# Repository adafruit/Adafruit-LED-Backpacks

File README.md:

# Adafruit LED Matrix backpacks PCBs

&nbsp; 
&nbsp; 
&nbsp; 
<br />
&nbsp; 
&nbsp; 
&nbsp; 
<br />

What's better than a single LED? Lots of LEDs! A fun way to make a small display is to use an 8x8 matrix or a 4-digit 7-segment display. Matrices like these are 'multiplexed' - so to control all the seven-segment LEDs you need 14 pins. That's a lot of pins, and there are driver chips like the MAX7219 that can control a matrix for you but there's a lot of wiring to set up and they take up a ton of space. Here at Adafruit we feel your pain! After all, wouldn't it be awesome if you could control a matrix without tons of wiring? That's where these adorable LED matrix backpacks come in. We have them in two flavors - a mini 8x8 and a 4-digit 0.56" 7-segment. 

These are the Eagle CAD files for the Adafruit LED Backpack breakouts:
- http://www.adafruit.com/products/878
- http://www.adafruit.com/products/879
- http://www.adafruit.com/products/880
- http://www.adafruit.com/products/881
- http://www.adafruit.com/products/872
- http://www.adafruit.com/products/871
- http://www.adafruit.com/products/870
- https://www.adafruit.com/product/902

These displays use I2C to communicate, 2 pins are required to 
interface. There are multiple selectable I2C addresses. For backpacks 
with 2 Address Select pins: 0x70, 0x71, 0x72 or 0x73. For backpacks 
with 3 Address Select pins: 0x70 thru 0x77

### License

Adafruit invests time and resources providing this open source design, please support Adafruit and open-source hardware by purchasing products from [Adafruit](https://www.adafruit.com)!

All text above must be included in any redistribution

Designed by Limor Fried/Ladyada for Adafruit Industries.
Creative Commons Attribution/Share-Alike, all text above must be included in any redistribution. 
See license.txt for additional information.

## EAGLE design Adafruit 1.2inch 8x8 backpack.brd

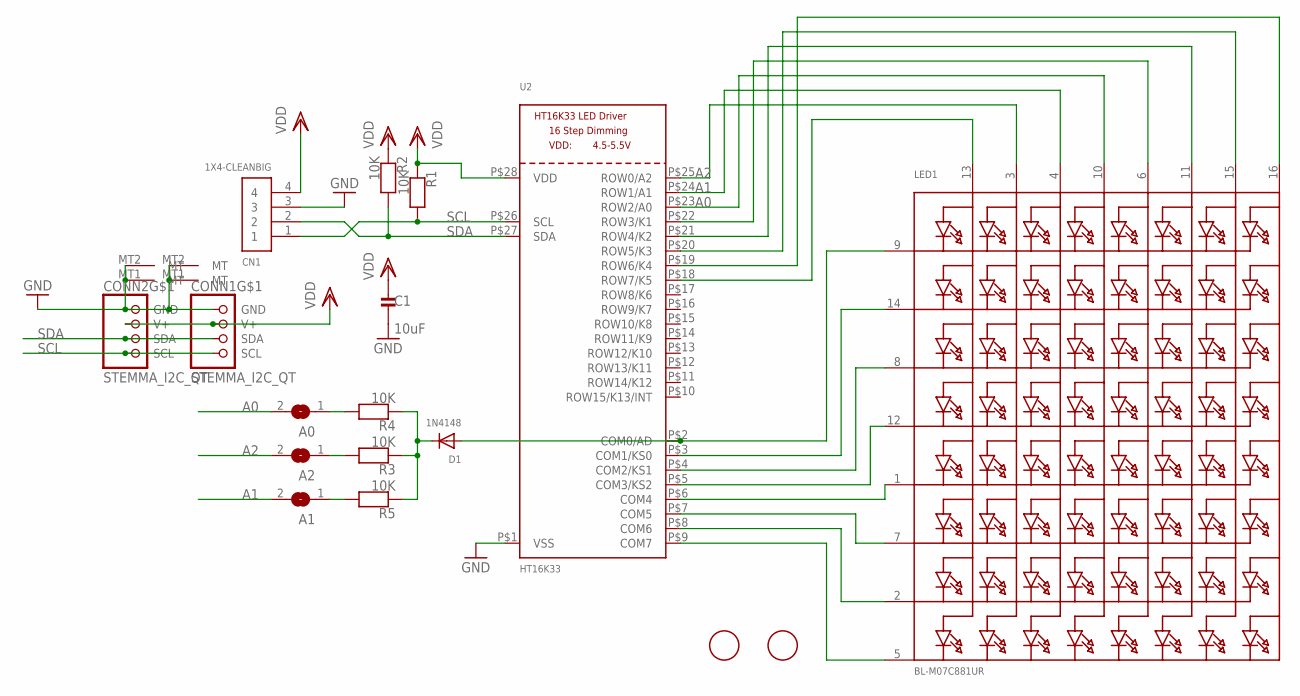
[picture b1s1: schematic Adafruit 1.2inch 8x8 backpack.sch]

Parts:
A0, A1, A2: SOLDERJUMPERREFLOW_NOPASTE; SOLDERJUMPER_REFLOW_NOPASTE
C1: 10uF; 0805-NO
CN1: 1X4-CLEANBIG; 1X04-CLEANBIG
CONN1, CONN2: STEMMA_I2C_QT; JST_SH4
D1: 1N4148; SOD-323
LED1: BL-M07C881UR; SEGMENT_BL-M12A881UR
R1, R2, R3, R4, R5: 10K; 0603-NO
U2: HT16K33; SOP28_300MIL
U$1, U$2: FIDUCIAL; FIDUCIAL_1MM

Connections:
A0: A0.2, LED1.10 (A4), U2.P$23 (ROW2/A0)
A1: A1.2, LED1.4 (A3), U2.P$24 (ROW1/A1)
A2: A2.2, LED1.3 (A2), U2.P$25 (ROW0/A2)
GND: C1.2, CN1.3, CONN1.1 (GND), CONN1.MT1 (MT), CONN1.MT2 (MT), CONN2.1 (GND), CONN2.MT1 (MT), CONN2.MT2 (MT), U2.P$1 (VSS)
unnamed: LED1.5 (K8), U2.P$9 (COM7)
unnamed: LED1.2 (K7), U2.P$8 (COM6)
unnamed: LED1.7 (K6), U2.P$7 (COM5)
unnamed: LED1.1 (K5), U2.P$6 (COM4)
unnamed: LED1.12 (K4), U2.P$5 (COM3/KS2)
unnamed: LED1.8 (K3), U2.P$4 (COM2/KS1)
unnamed: LED1.14 (K2), U2.P$3 (COM1/KS0)
unnamed: D1.A, LED1.9 (K1), U2.P$2 (COM0/AD)
unnamed: A1.1, R5.2
unnamed: LED1.6 (A5), U2.P$22 (ROW3/K1)
unnamed: LED1.11 (A6), U2.P$21 (ROW4/K2)
unnamed: D1.C, R3.1, R4.1, R5.1
unnamed: LED1.13 (A1), U2.P$18 (ROW7/K5)
unnamed: A2.1, R3.2
unnamed: A0.1, R4.2
SCL: CN1.1, CONN1.4 (SCL), CONN2.4 (SCL), R1.2, U2.P$26 (SCL)
SDA: CN1.2, CONN1.3 (SDA), CONN2.3 (SDA), R2.2, U2.P$27 (SDA)
SEG_F: LED1.15 (A7), U2.P$20 (ROW5/K3)
SEG_G: LED1.16 (A8), U2.P$19 (ROW6/K4)
VDD: C1.1, CN1.4, CONN1.2 (V+), CONN2.2 (V+), R1.1, R2.1, U2.P$28 (VDD)

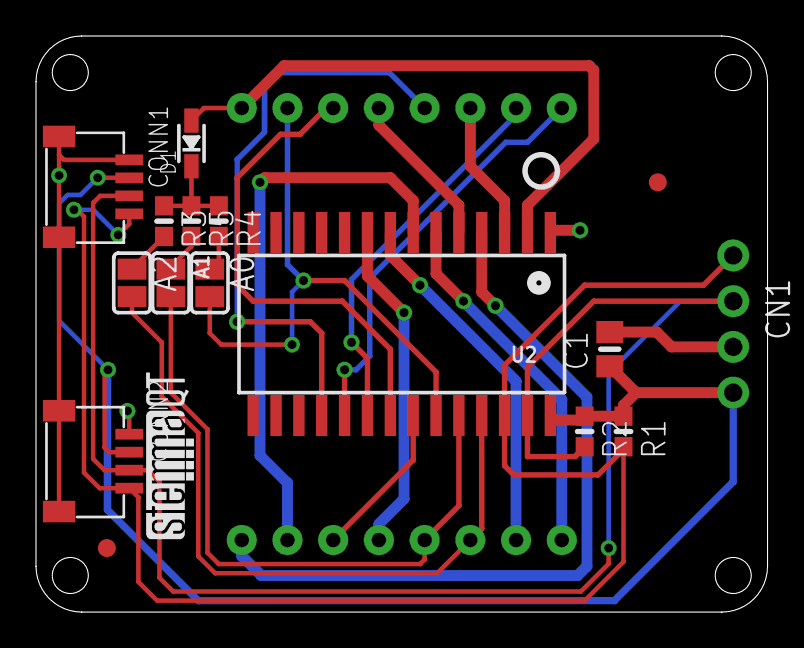
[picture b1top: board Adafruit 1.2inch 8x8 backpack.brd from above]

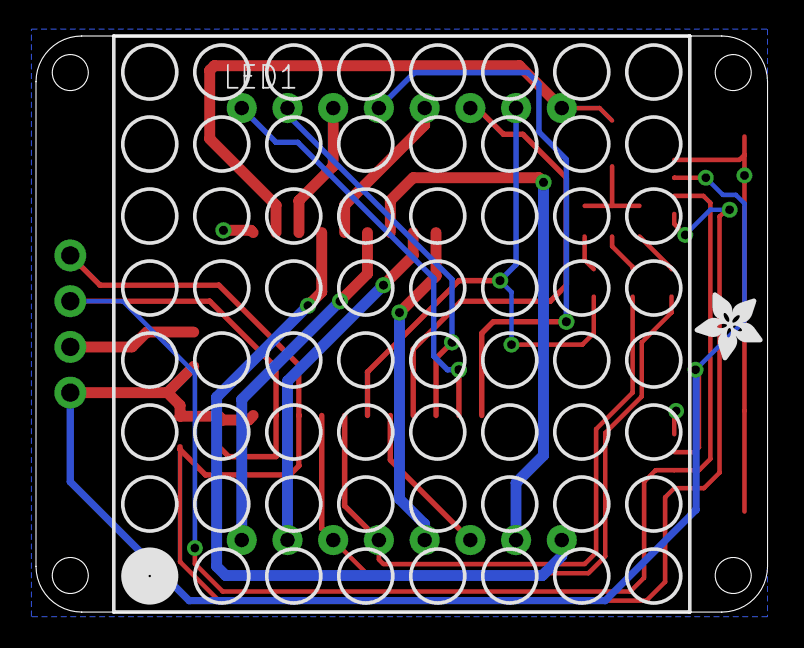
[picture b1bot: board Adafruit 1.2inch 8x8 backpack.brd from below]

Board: 2 copper layers, 40.6 x 32.0 mm, 34 parts (6 on the bottom side), 24 nets.

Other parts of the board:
PLABEL0: PLABEL0
PLABEL1: PLABEL1
PLABEL2: PLABEL2
PLABEL3: PLABEL3
PLABEL4: PLABEL4
PLABEL5: PLABEL5
PLABEL6: PLABEL6
PLABEL7: PLABEL7
PLABEL8: PLABEL8
PLABEL9: PLABEL9
PLABEL10: PLABEL10
PLABEL11: PLABEL11
PLABEL12: PLABEL12
PLABEL13: PLABEL13
U$3: ADAFRUIT_3.5MM
U$4: PCBFEAT-REV-040
U$5: STEMMAQT

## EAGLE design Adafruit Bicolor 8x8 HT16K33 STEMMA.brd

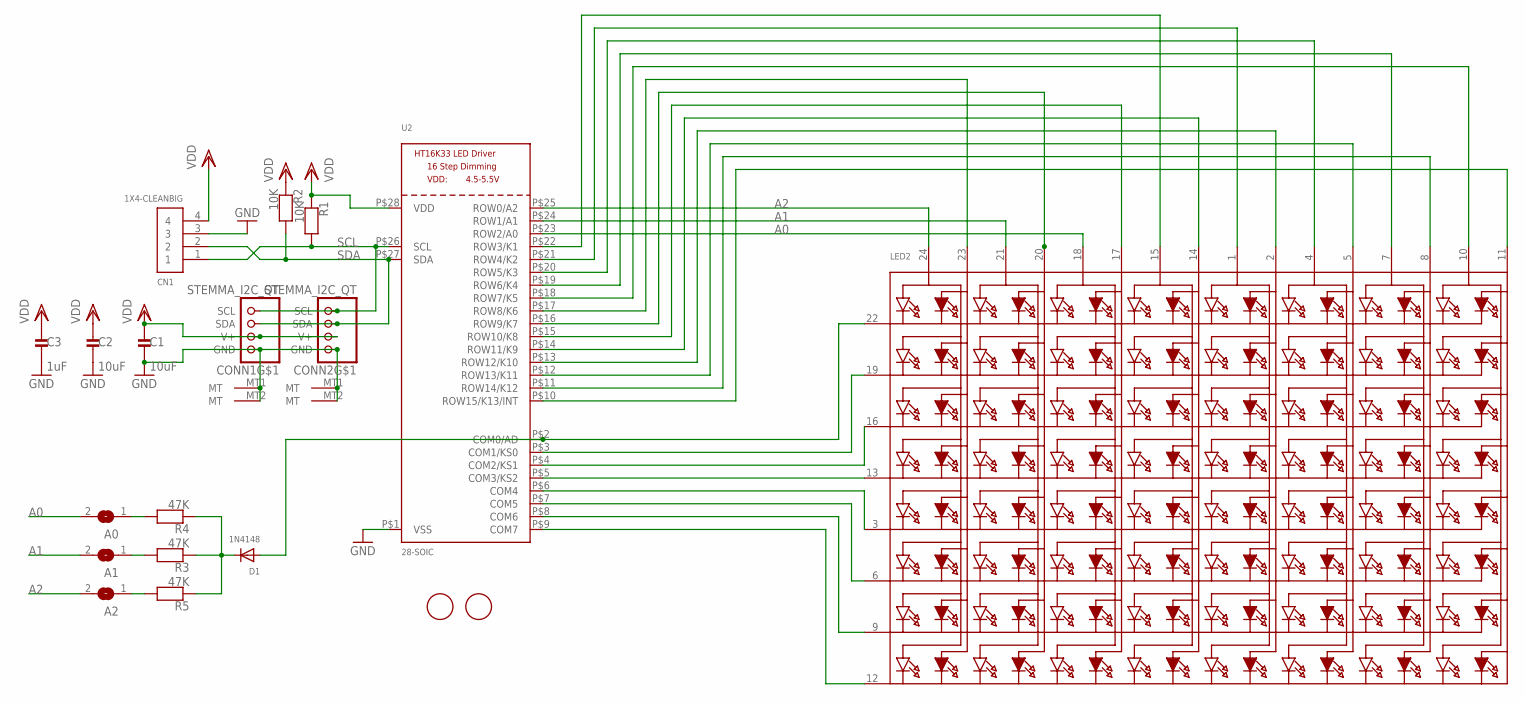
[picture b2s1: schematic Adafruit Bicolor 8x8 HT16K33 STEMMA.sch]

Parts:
A0, A1, A2: SOLDERJUMPERREFLOW_NOPASTE; SOLDERJUMPER_REFLOW_NOPASTE
C1, C2: 10uF; 0805-NO
C3: 1uF; 0603-NO
CN1: 1X4-CLEANBIG; 1X04-CLEANBIG
CONN1, CONN2: STEMMA_I2C_QT; JST_SH4
D1: 1N4148; SOD-323
LED2: DISP_SEGMENT_8X8_BICOLOR_ROWCATHODEMI2A883XX; SEGMENT_BICOL_BL-M12A883XX
R1, R2: 10K; 0603-NO
R3, R4, R5: 47K; 0603-NO
U2: 28-SOIC; SOP28_300MIL
U$1, U$2: FIDUCIAL; FIDUCIAL_1MM

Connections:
A0: A0.2, LED2.18 (A5), U2.P$23 (ROW2/A0)
A1: A1.2, LED2.21 (A3), U2.P$24 (ROW1/A1)
A2: A2.2, LED2.24 (A1), U2.P$25 (ROW0/A2)
GND: C1.2, C2.2, C3.2, CN1.3, CONN1.1 (GND), CONN1.MT1 (MT), CONN1.MT2 (MT), CONN2.1 (GND), CONN2.MT1 (MT), CONN2.MT2 (MT), U2.P$1 (VSS)
unnamed: LED2.12 (K8), U2.P$9 (COM7)
unnamed: LED2.9 (K7), U2.P$8 (COM6)
unnamed: LED2.6 (K6), U2.P$7 (COM5)
unnamed: LED2.3 (K5), U2.P$6 (COM4)
unnamed: LED2.13 (K4), U2.P$5 (COM3/KS2)
unnamed: LED2.16 (K3), U2.P$4 (COM2/KS1)
unnamed: LED2.19 (K2), U2.P$3 (COM1/KS0)
unnamed: D1.A, LED2.22 (K1), U2.P$2 (COM0/AD)
unnamed: A2.1, R5.2
unnamed: LED2.8 (A14), U2.P$11 (ROW14/K12)
unnamed: LED2.5 (A12), U2.P$12 (ROW13/K11)
unnamed: LED2.11 (A16), U2.P$10 (ROW15/K13/INT)
unnamed: D1.C, R3.1, R4.1, R5.1
unnamed: A1.1, R3.2
unnamed: A0.1, R4.2
unnamed: LED2.10 (A15), U2.P$18 (ROW7/K5)
unnamed: LED2.7 (A13), U2.P$19 (ROW6/K4)
unnamed: LED2.1 (A9), U2.P$21 (ROW4/K2)
unnamed: LED2.15 (A7), U2.P$22 (ROW3/K1)
unnamed: LED2.4 (A11), U2.P$20 (ROW5/K3)
unnamed: LED2.23 (A2), U2.P$17 (ROW8/K6)
unnamed: LED2.20 (A4), U2.P$16 (ROW9/K7)
unnamed: LED2.14 (A8), U2.P$14 (ROW11/K9)
unnamed: LED2.17 (A6), U2.P$15 (ROW10/K8)
unnamed: LED2.2 (A10), U2.P$13 (ROW12/K10)
SCL: CN1.1, CONN1.4 (SCL), CONN2.4 (SCL), R1.2, U2.P$26 (SCL)
SDA: CN1.2, CONN1.3 (SDA), CONN2.3 (SDA), R2.2, U2.P$27 (SDA)
VDD: C1.1, C2.1, C3.1, CN1.4, CONN1.2 (V+), CONN2.2 (V+), R1.1, R2.1, U2.P$28 (VDD)

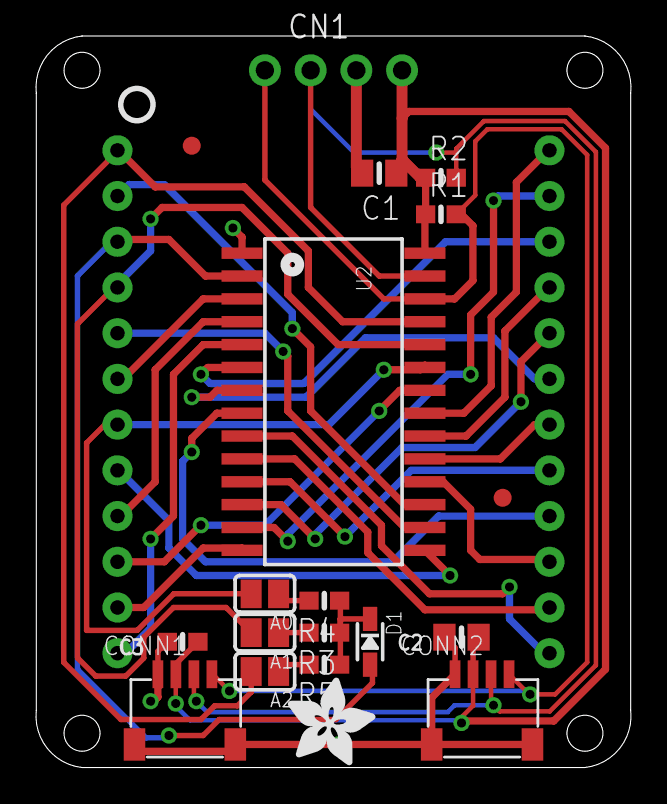
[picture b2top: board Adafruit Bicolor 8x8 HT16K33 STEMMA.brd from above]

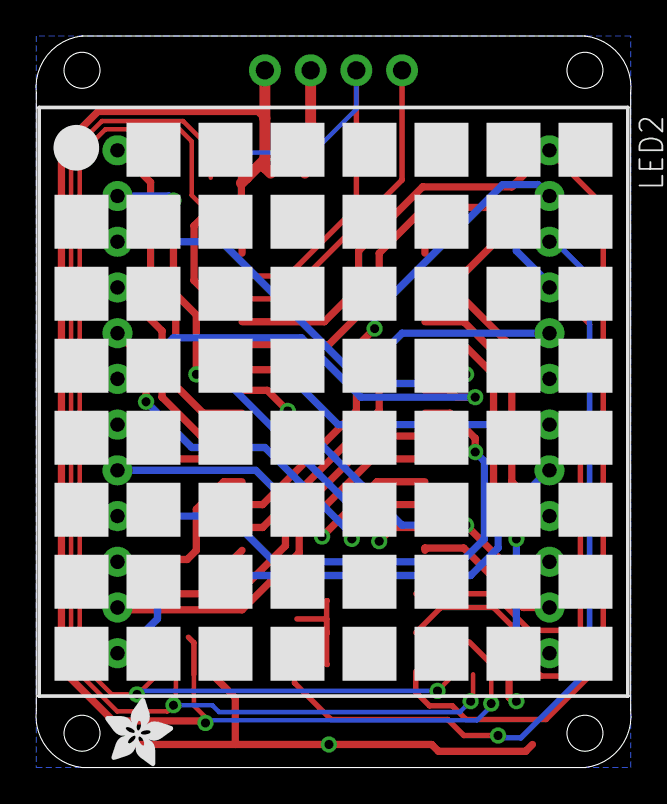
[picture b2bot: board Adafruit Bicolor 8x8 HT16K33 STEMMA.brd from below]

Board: 2 copper layers, 33.1 x 40.6 mm, 37 parts (7 on the bottom side), 32 nets.

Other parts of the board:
E$2: ADAFRUIT_3.5MM
PLABEL0: PLABEL0
PLABEL1: PLABEL1
PLABEL2: PLABEL2
PLABEL3: PLABEL3
PLABEL4: PLABEL4
PLABEL5: PLABEL5
PLABEL6: PLABEL6
PLABEL7: PLABEL7
PLABEL8: PLABEL8
PLABEL9: PLABEL9
PLABEL10: PLABEL10
PLABEL11: PLABEL11
PLABEL12: PLABEL12
PLABEL13: PLABEL13
PLABEL14: PLABEL14
U$3: ADAFRUIT_5MM
U$4: PCBFEAT-REV-040

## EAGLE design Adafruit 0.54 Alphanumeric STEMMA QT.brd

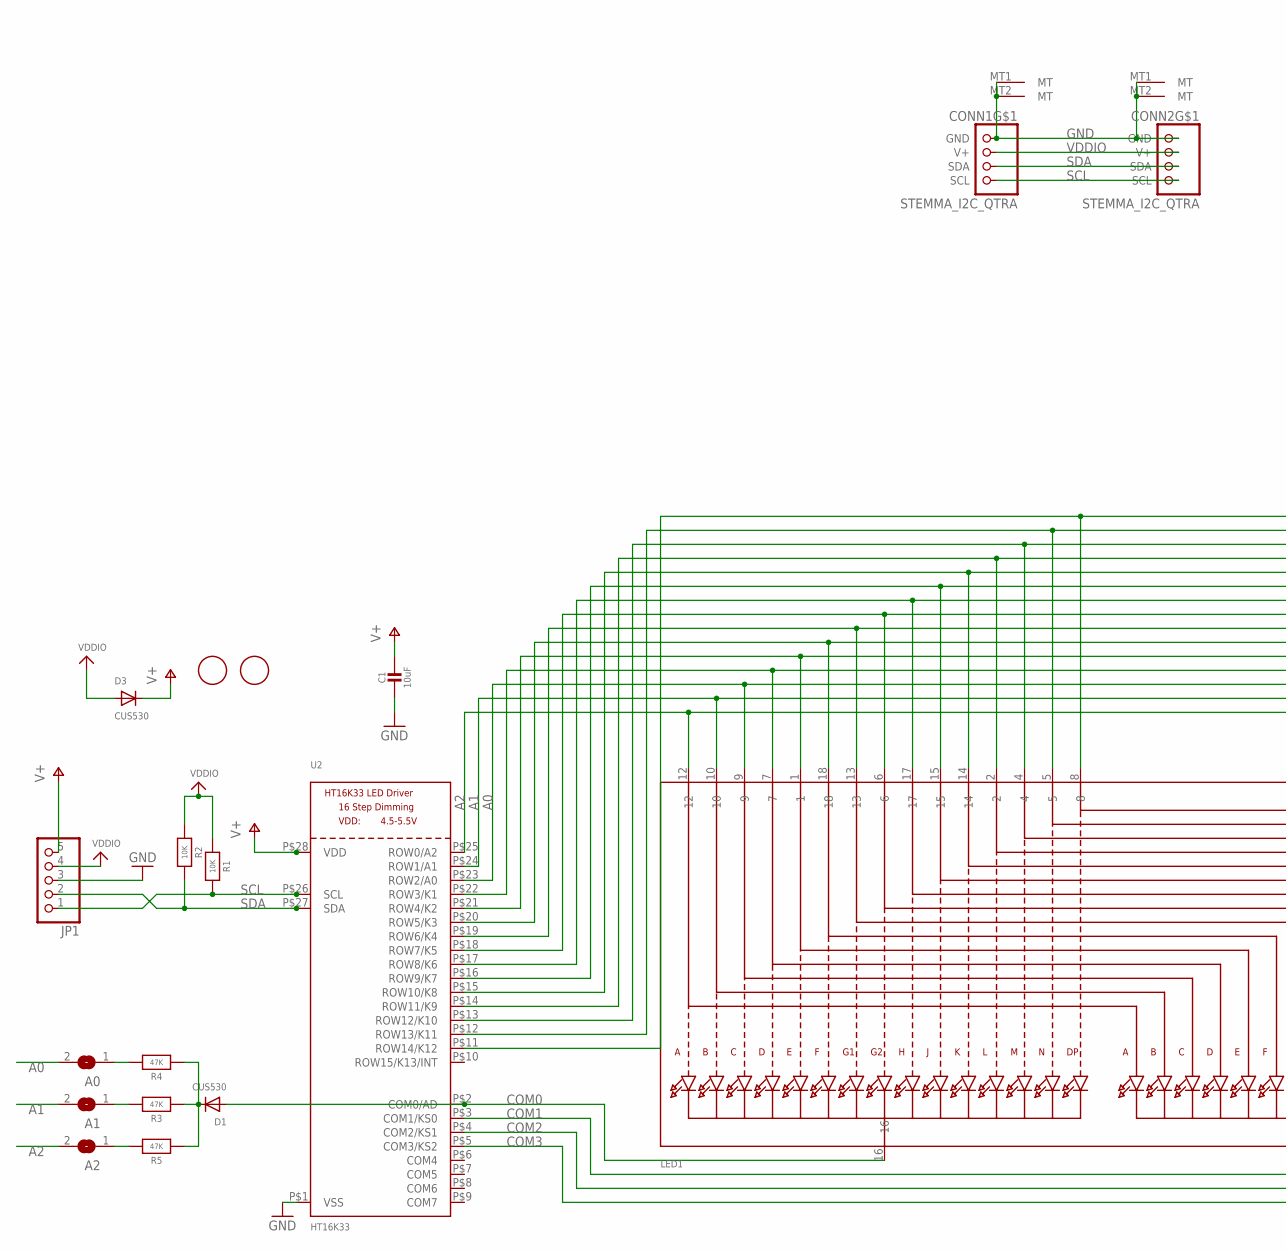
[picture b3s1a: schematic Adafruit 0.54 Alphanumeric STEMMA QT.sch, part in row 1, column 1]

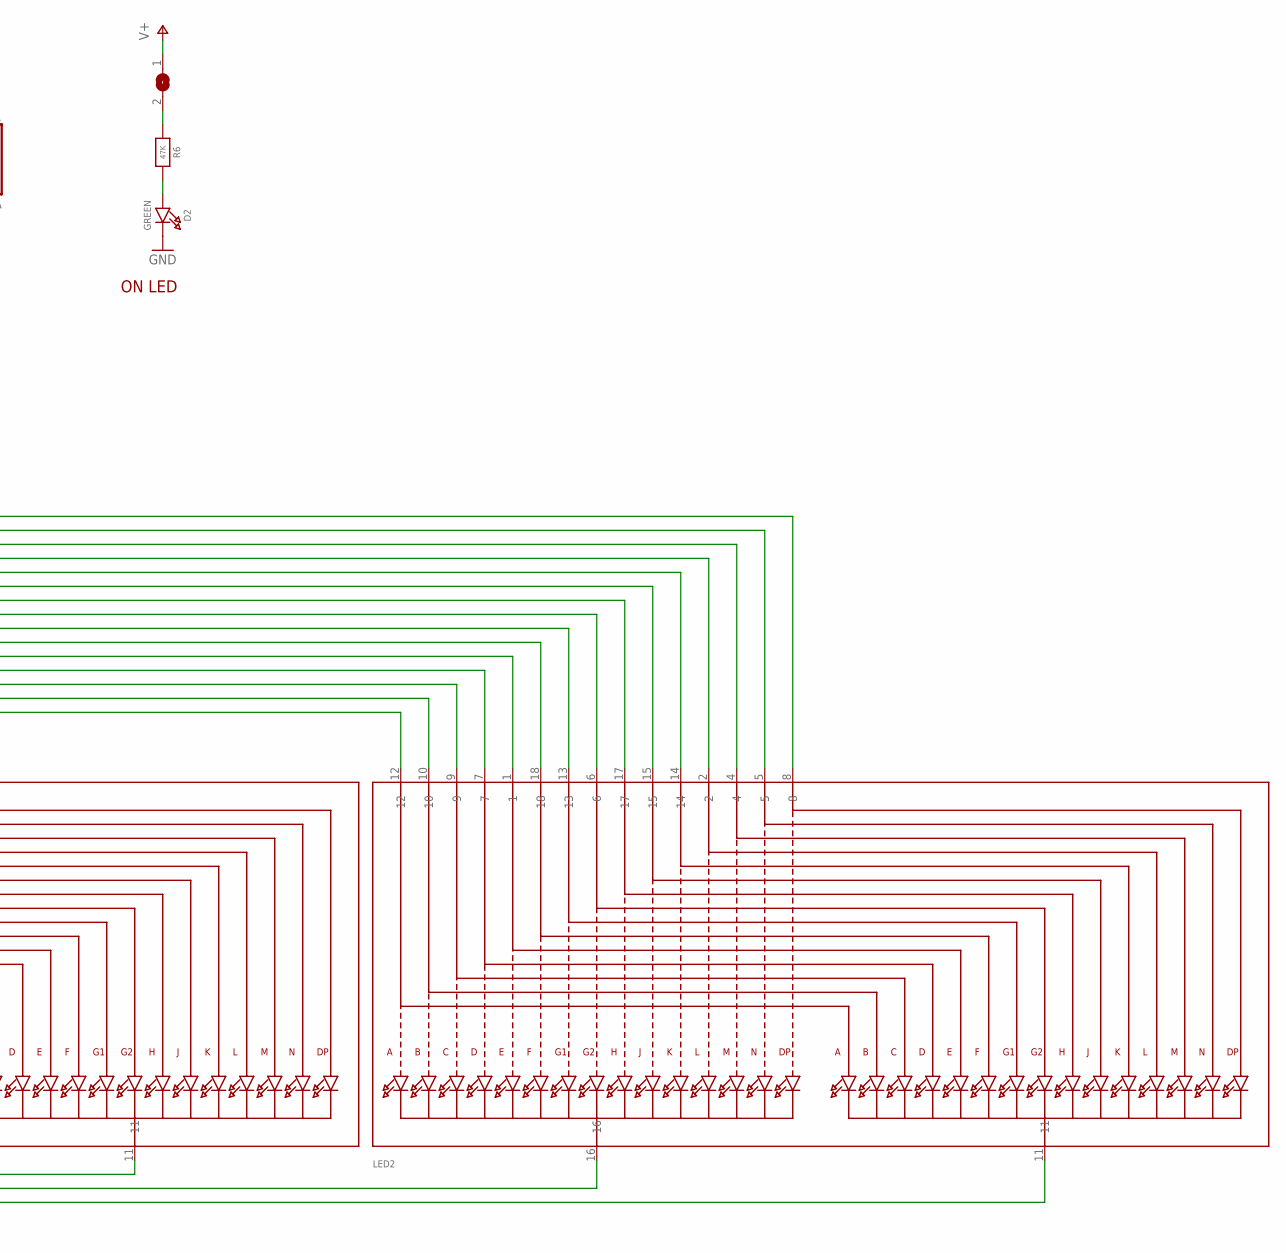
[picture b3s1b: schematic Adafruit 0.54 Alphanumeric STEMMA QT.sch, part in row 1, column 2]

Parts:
A0, A1, A2: SOLDERJUMPERREFLOW_NOPASTE; SOLDERJUMPER_REFLOW_NOPASTE
C1: 10uF; 0805-NO
CONN1, CONN2: STEMMA_I2C_QTRA; JST_SH4_RA
D1, D3: CUS530; SOD-323F
D2: GREEN; CHIPLED_0603_NOOUTLINE
JP1: HEADER-1X570MIL; 1X05_ROUND_70
LED1, LED2: DISP_SEGMENT_STARBURST_DUAL_COMMONCATHODE; SEGMENT_STARTBUST_DUAL_KWA-541CBB
LEDJMP: SOLDERJUMPERCLOSED; SOLDERJUMPER_CLOSEDWIRE
R1, R2: 10K; 0603-NO
R3, R4, R5, R6: 47K; 0603-NO
U2: HT16K33; SOP28_300MIL_SKINNY
U$1, U$2: FIDUCIAL; FIDUCIAL_1MM

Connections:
A0: A0.2, LED1.9, LED2.9, U2.P$23 (ROW2/A0)
A1: A1.2, LED1.10, LED2.10, U2.P$24 (ROW1/A1)
A2: A2.2, LED1.12, LED2.12, U2.P$25 (ROW0/A2)
COM0: D1.A, LED1.16, U2.P$2 (COM0/AD)
COM1: LED1.11, U2.P$3 (COM1/KS0)
COM2: LED2.16, U2.P$4 (COM2/KS1)
COM3: LED2.11, U2.P$5 (COM3/KS2)
GND: C1.2, CONN1.1 (GND), CONN1.MT1 (MT), CONN1.MT2 (MT), CONN2.1 (GND), CONN2.MT1 (MT), CONN2.MT2 (MT), D2.C, JP1.3, U2.P$1 (VSS)
unnamed: D1.C, R3.1, R4.1, R5.1
unnamed: D2.A, R6.2
unnamed: LED1.17, LED2.17, U2.P$17 (ROW8/K6)
unnamed: LED1.15, LED2.15, U2.P$16 (ROW9/K7)
unnamed: LED1.14, LED2.14, U2.P$15 (ROW10/K8)
unnamed: A2.1, R5.2
unnamed: LED1.2, LED2.2, U2.P$14 (ROW11/K9)
unnamed: LED1.4, LED2.4, U2.P$13 (ROW12/K10)
unnamed: LED1.7, LED2.7, U2.P$22 (ROW3/K1)
unnamed: LED1.1, LED2.1, U2.P$21 (ROW4/K2)
unnamed: LED1.18, LED2.18, U2.P$20 (ROW5/K3)
unnamed: LED1.13, LED2.13, U2.P$19 (ROW6/K4)
unnamed: LED1.5, LED2.5, U2.P$12 (ROW13/K11)
unnamed: LED1.8, LED2.8, U2.P$11 (ROW14/K12)
unnamed: LED1.6, LED2.6, U2.P$18 (ROW7/K5)
unnamed: LEDJMP.2, R6.1
unnamed: A1.1, R3.2
unnamed: A0.1, R4.2
SCL: CONN1.4 (SCL), CONN2.4 (SCL), JP1.1, R1.2, U2.P$26 (SCL)
SDA: CONN1.3 (SDA), CONN2.3 (SDA), JP1.2, R2.2, U2.P$27 (SDA)
V+: C1.1, D3.C, JP1.5, LEDJMP.1, U2.P$28 (VDD)
VDDIO: CONN1.2 (V+), CONN2.2 (V+), D3.A, JP1.4, R1.1, R2.1

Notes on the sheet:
ON LED

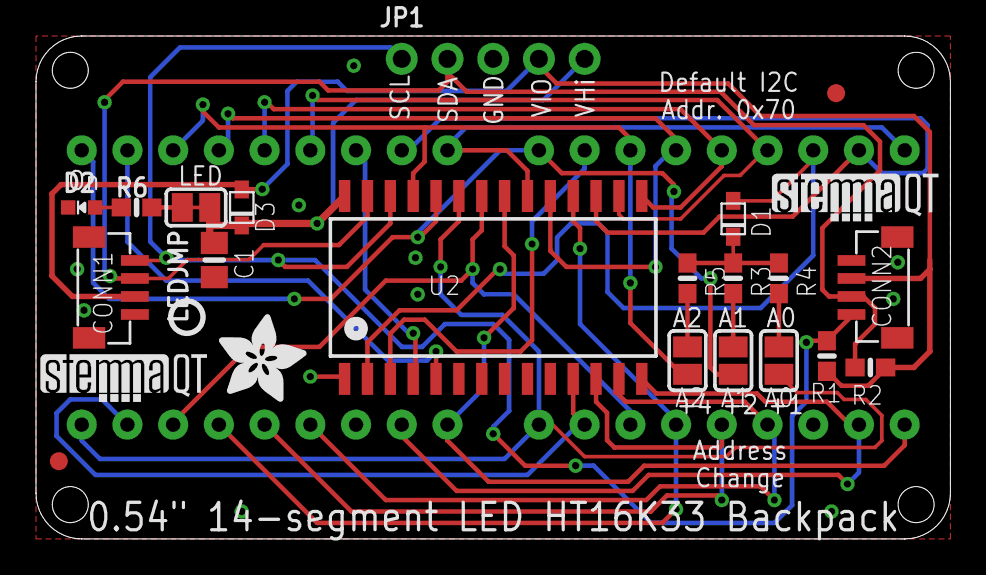
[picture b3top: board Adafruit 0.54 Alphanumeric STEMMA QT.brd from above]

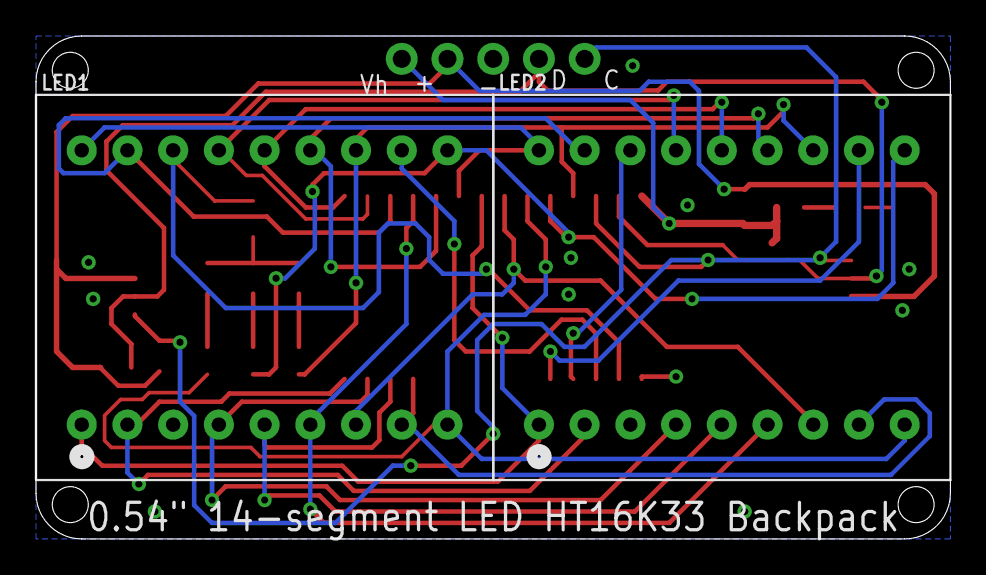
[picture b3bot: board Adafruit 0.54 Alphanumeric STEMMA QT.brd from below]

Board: 2 copper layers, 50.8 x 27.9 mm, 26 parts (2 on the bottom side), 30 nets.

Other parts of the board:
U$3: ADAFRUIT_5MM
U$6, U$7: STEMMAQT
U$8: PCBFEAT-REV-040

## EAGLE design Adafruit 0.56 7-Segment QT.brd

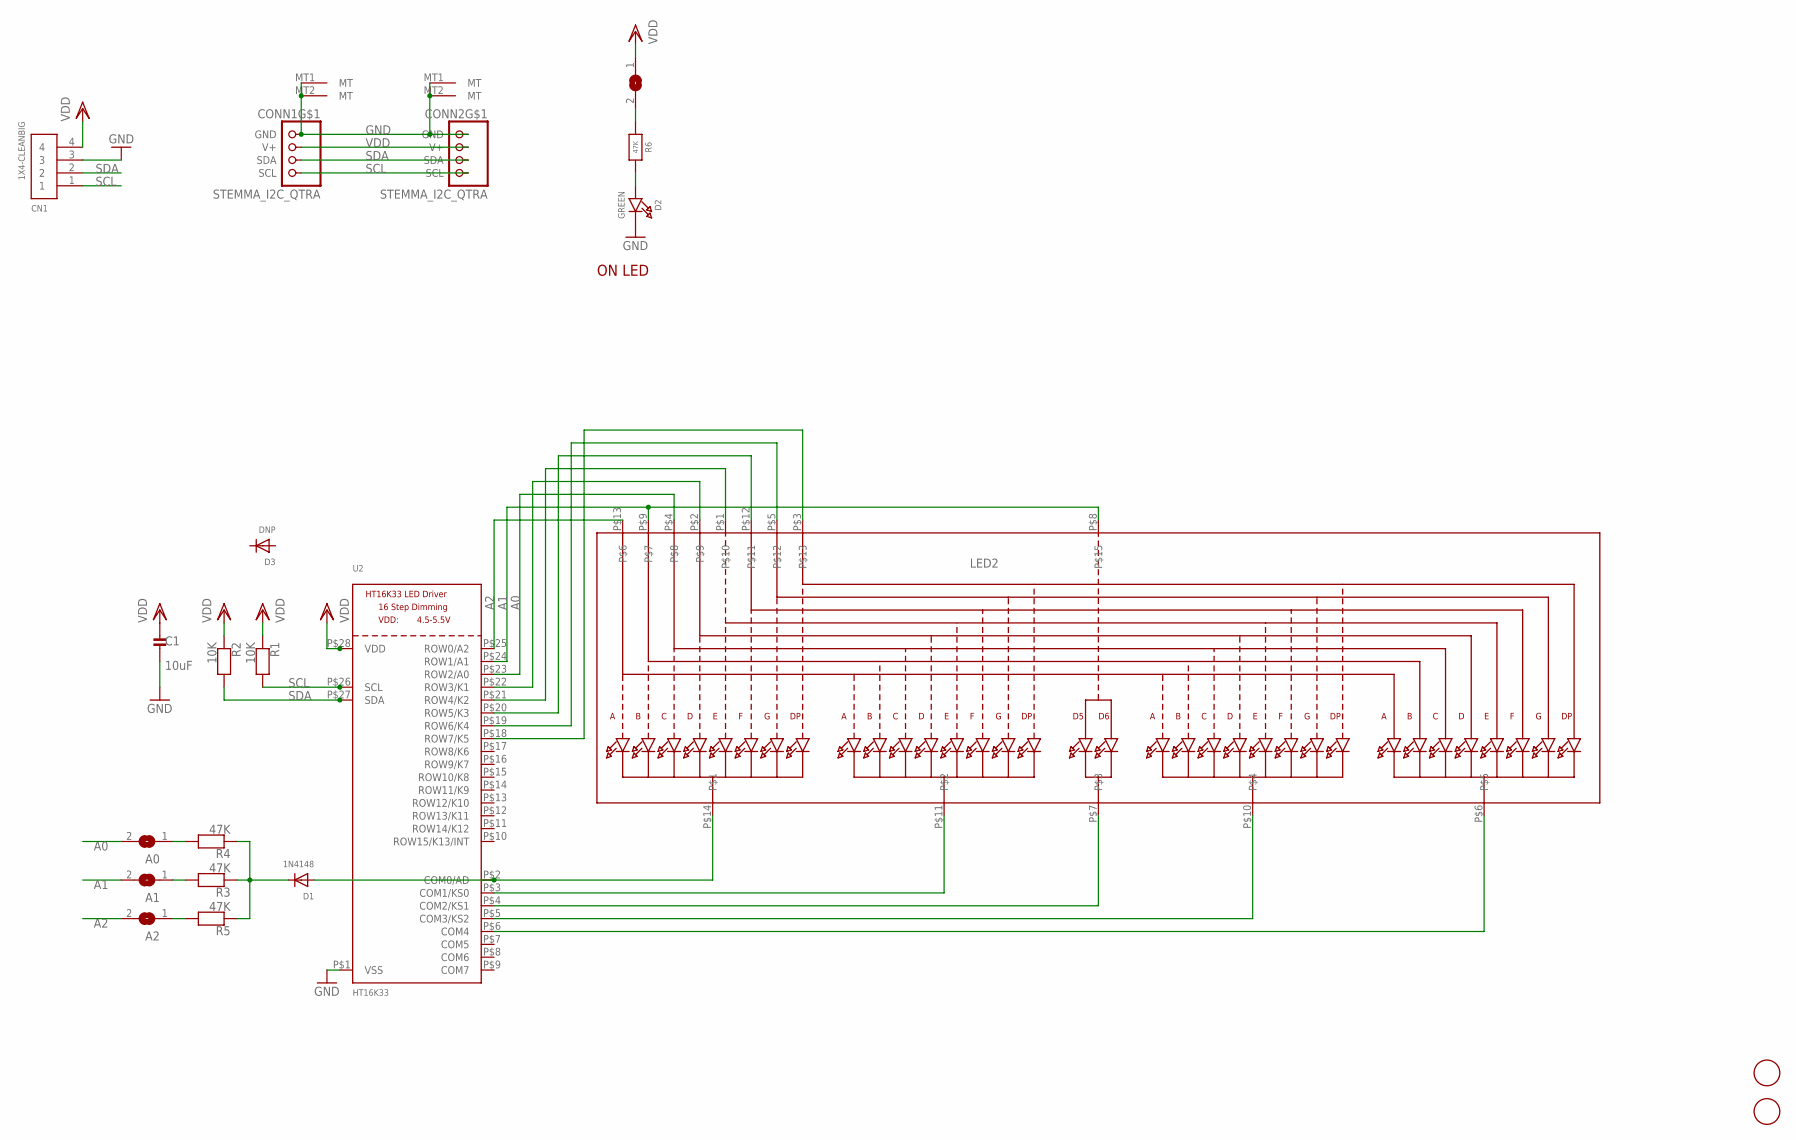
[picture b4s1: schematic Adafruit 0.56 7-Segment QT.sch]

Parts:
A0, A1, A2: SOLDERJUMPER; SOLDERJUMPER_ARROW_NOPASTE
C1: 10uF; 0805_10MGAP
CN1: 1X4-CLEANBIG; 1X04-CLEANBIG
CONN1, CONN2: STEMMA_I2C_QTRA; JST_SH4_RA
D1: 1N4148; SOD-323F
D2: GREEN; CHIPLED_0603_NOOUTLINE
D3: DNP; SOD-323F
LED2: DISP_SEGMENT_4DIGIT_BL-Q56C43; SEGMENT-BL-Q56C43
LEDJMP: SOLDERJUMPERCLOSED; SOLDERJUMPER_CLOSEDWIRE
R1, R2: 10K; 0603-NO
R3, R4, R5, R6: 47K; 0603-NO
U2: HT16K33; SOP28_300MIL_SKINNY
U$1, U$2: FIDUCIAL; FIDUCIAL_1MM

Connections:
A0: A0.2, LED2.P$4, U2.P$23 (ROW2/A0)
A1: A1.2, LED2.P$8, LED2.P$9, U2.P$24 (ROW1/A1)
A2: A2.2, LED2.P$13, U2.P$25 (ROW0/A2)
GND: C1.2, CN1.3, CONN1.1 (GND), CONN1.MT1 (MT), CONN1.MT2 (MT), CONN2.1 (GND), CONN2.MT1 (MT), CONN2.MT2 (MT), D2.C, U2.P$1 (VSS)
unnamed: D1.C, R3.1, R4.1, R5.1
unnamed: D1.A, LED2.P$14, U2.P$2 (COM0/AD)
unnamed: LED2.P$11, U2.P$3 (COM1/KS0)
unnamed: LED2.P$7, U2.P$4 (COM2/KS1)
unnamed: LED2.P$10, U2.P$5 (COM3/KS2)
unnamed: LED2.P$6, U2.P$6 (COM4)
unnamed: A2.1, R5.2
unnamed: D2.A, R6.2
unnamed: LEDJMP.2, R6.1
unnamed: LED2.P$2, U2.P$22 (ROW3/K1)
unnamed: LED2.P$1, U2.P$21 (ROW4/K2)
unnamed: LED2.P$12, U2.P$20 (ROW5/K3)
unnamed: LED2.P$5, U2.P$19 (ROW6/K4)
unnamed: LED2.P$3, U2.P$18 (ROW7/K5)
unnamed: A1.1, R3.2
unnamed: A0.1, R4.2
SCL: CN1.1, CONN1.4 (SCL), CONN2.4 (SCL), R1.2, U2.P$26 (SCL)
SDA: CN1.2, CONN1.3 (SDA), CONN2.3 (SDA), R2.2, U2.P$27 (SDA)
VDD: C1.1, CN1.4, CONN1.2 (V+), CONN2.2 (V+), LEDJMP.1, R1.1, R2.1, U2.P$28 (VDD)

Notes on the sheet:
ON LED

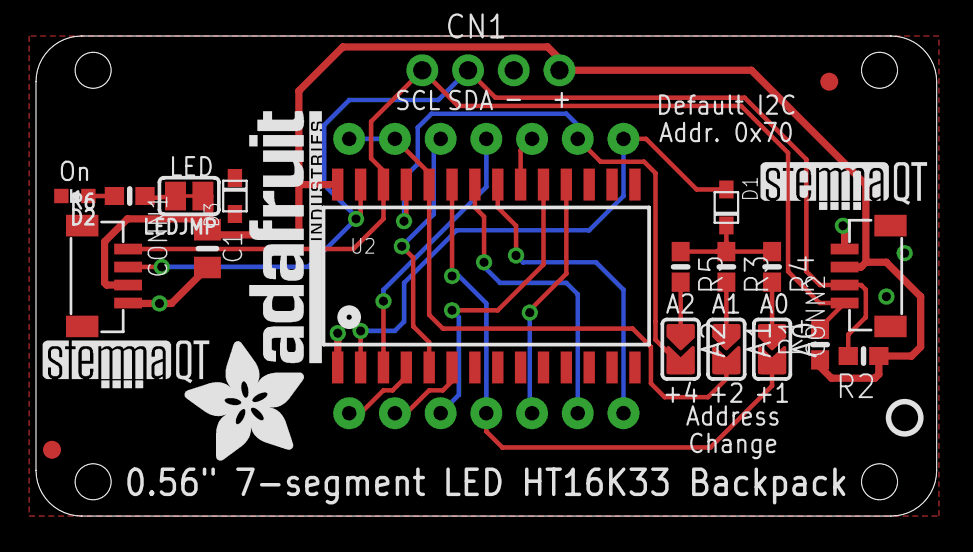
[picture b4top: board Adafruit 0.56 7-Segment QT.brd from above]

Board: 2 copper layers, 50.0 x 26.7 mm, 25 parts (1 on the bottom side), 23 nets.

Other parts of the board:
U$3: ADAFRUIT_TEXT_20MM
U$5, U$6: STEMMAQT
U$7: PCBFEAT-REV-040

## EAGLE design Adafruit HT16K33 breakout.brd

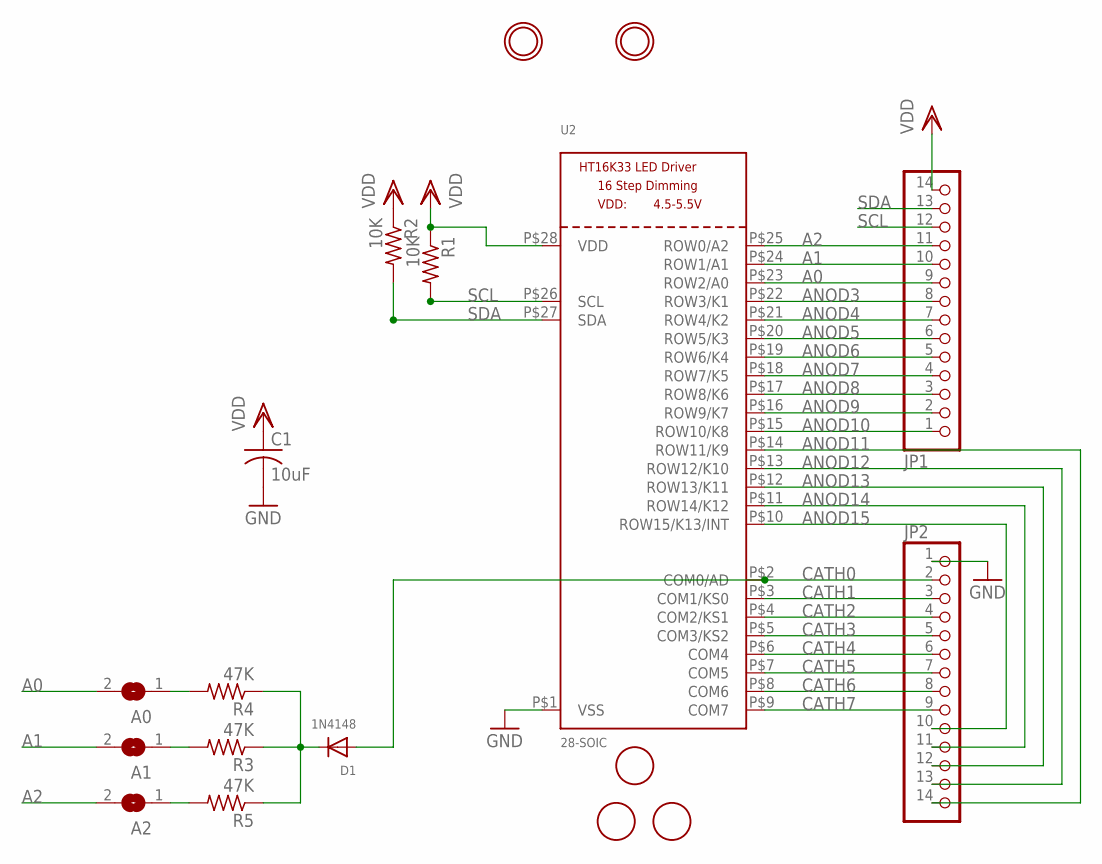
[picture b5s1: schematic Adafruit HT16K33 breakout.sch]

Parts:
A0, A1, A2: SOLDERJUMPERREFLOW_NOPASTE; SOLDERJUMPER_REFLOW_NOPASTE
C1: 10uF; C0805
D1: 1N4148; SOD-323F
JP1, JP2: PINHD-1X14-CB; 1X14-CB
R1, R2: 10K; R0805
R3, R4, R5: 47K; R0805
U2: 28-SOIC; SOP28_300MIL
U$1, U$2, U$6: FIDUCIAL; FIDUCIAL_1MM
U$4, U$5: MOUNTINGHOLE2.5; MOUNTINGHOLE_2.5_PLATED

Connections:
A0: A0.2, JP1.9, U2.P$23 (ROW2/A0)
A1: A1.2, JP1.10, U2.P$24 (ROW1/A1)
A2: A2.2, JP1.11, U2.P$25 (ROW0/A2)
ANOD3: JP1.8, U2.P$22 (ROW3/K1)
ANOD4: JP1.7, U2.P$21 (ROW4/K2)
ANOD5: JP1.6, U2.P$20 (ROW5/K3)
ANOD6: JP1.5, U2.P$19 (ROW6/K4)
ANOD7: JP1.4, U2.P$18 (ROW7/K5)
ANOD8: JP1.3, U2.P$17 (ROW8/K6)
ANOD9: JP1.2, U2.P$16 (ROW9/K7)
ANOD10: JP1.1, U2.P$15 (ROW10/K8)
ANOD11: JP2.14, U2.P$14 (ROW11/K9)
ANOD12: JP2.13, U2.P$13 (ROW12/K10)
ANOD13: JP2.12, U2.P$12 (ROW13/K11)
ANOD14: JP2.11, U2.P$11 (ROW14/K12)
ANOD15: JP2.10, U2.P$10 (ROW15/K13/INT)
CATH0: D1.A, JP2.2, U2.P$2 (COM0/AD)
CATH1: JP2.3, U2.P$3 (COM1/KS0)
CATH2: JP2.4, U2.P$4 (COM2/KS1)
CATH3: JP2.5, U2.P$5 (COM3/KS2)
CATH4: JP2.6, U2.P$6 (COM4)
CATH5: JP2.7, U2.P$7 (COM5)
CATH6: JP2.8, U2.P$8 (COM6)
CATH7: JP2.9, U2.P$9 (COM7)
GND: C1.2, JP2.1, U2.P$1 (VSS)
unnamed: A2.1, R5.2
unnamed: D1.C, R3.1, R4.1, R5.1
unnamed: A1.1, R3.2
unnamed: A0.1, R4.2
SCL: JP1.12, R1.2, U2.P$26 (SCL)
SDA: JP1.13, R2.2, U2.P$27 (SDA)
VDD: C1.1, JP1.14, R1.1, R2.1, U2.P$28 (VDD)

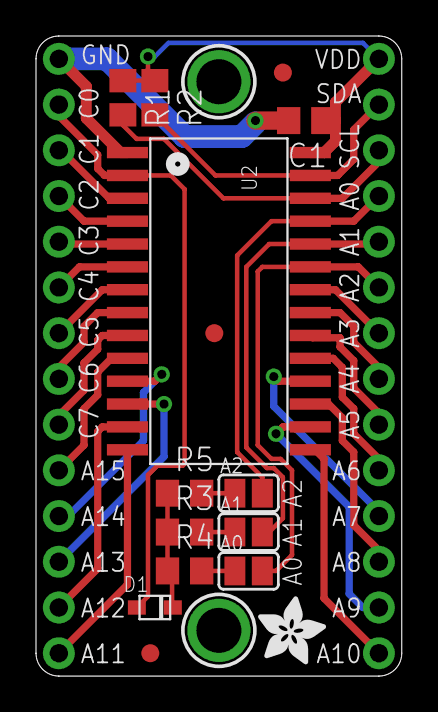
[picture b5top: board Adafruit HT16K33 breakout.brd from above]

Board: 2 copper layers, 20.3 x 35.6 mm, 20 parts (1 on the bottom side), 32 nets.

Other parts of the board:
U$3: ADAFRUIT_3.5MM
U$7: ADAFRUIT_5MM

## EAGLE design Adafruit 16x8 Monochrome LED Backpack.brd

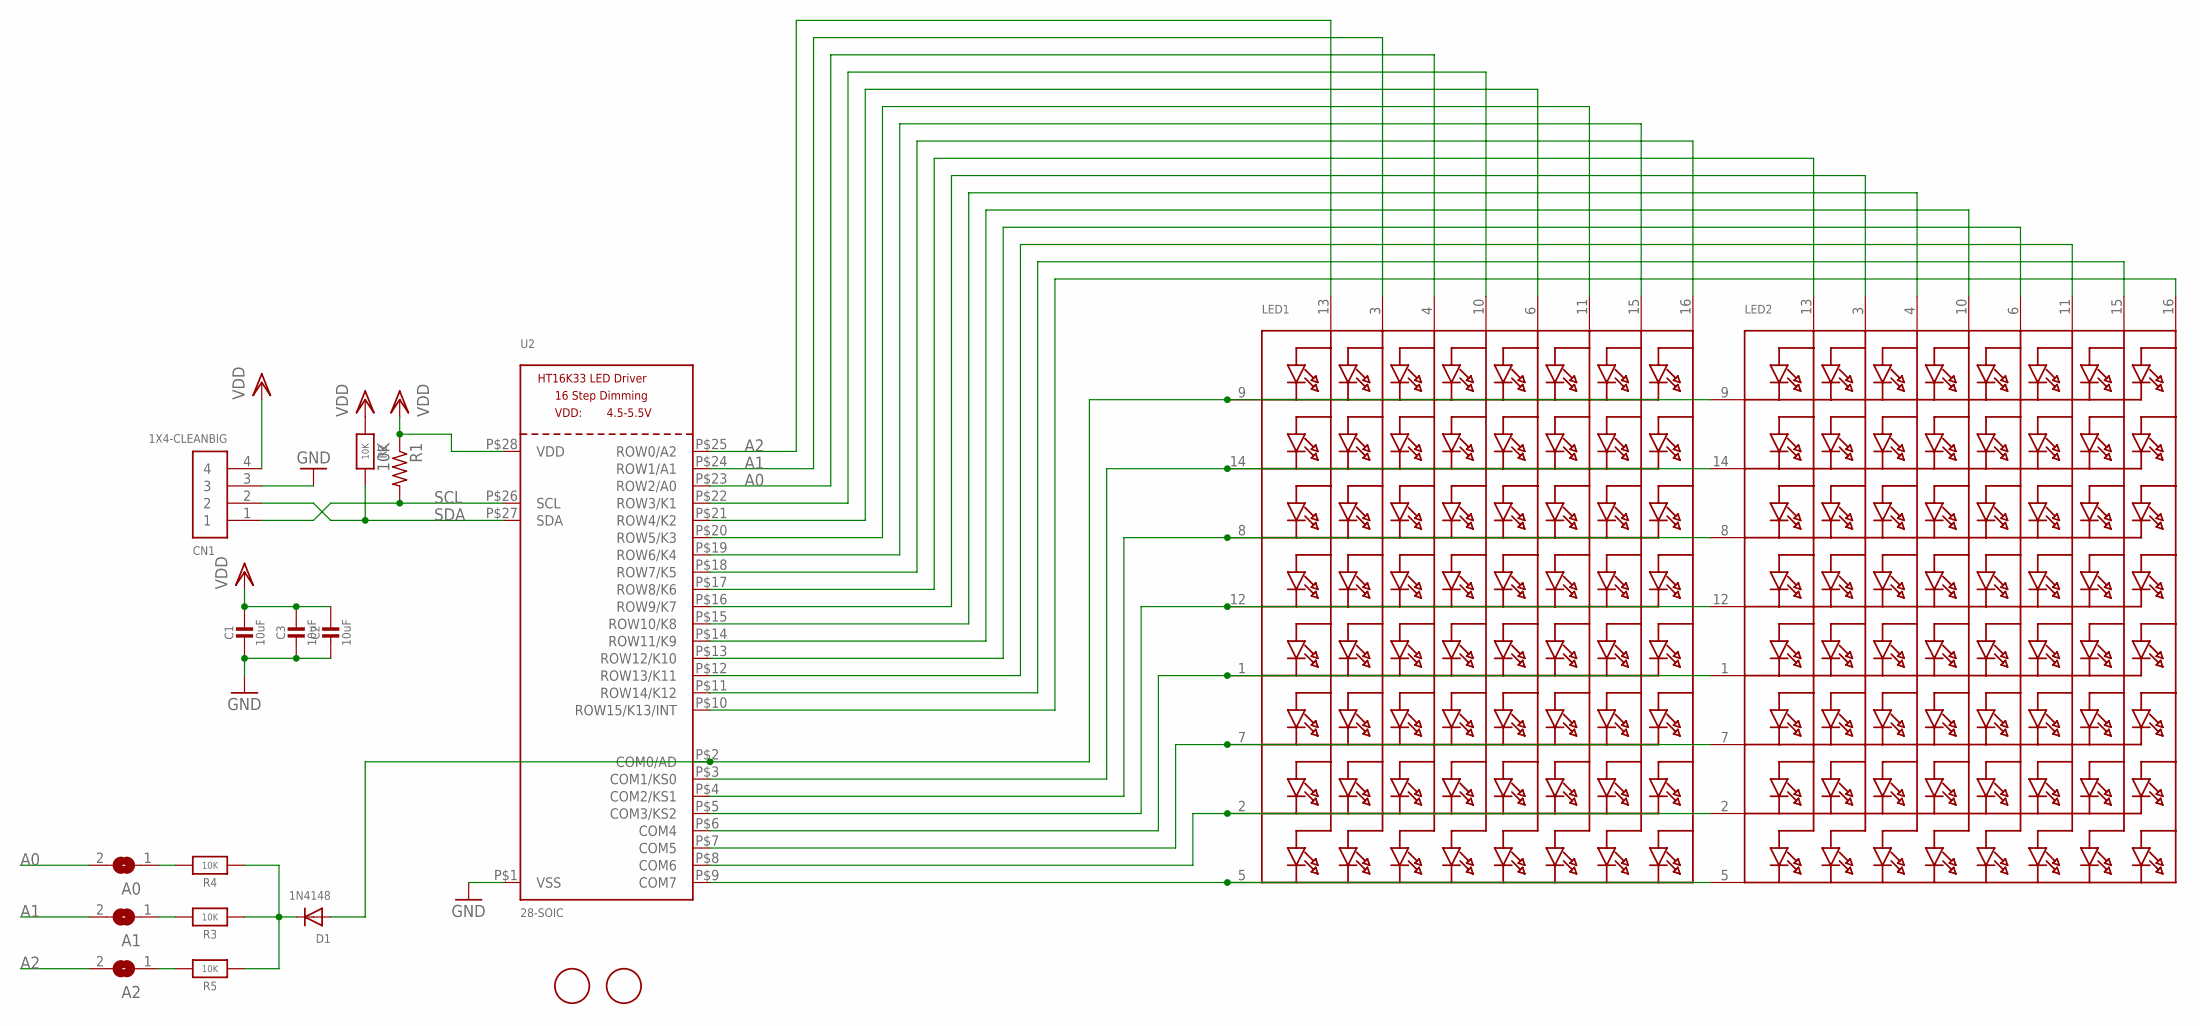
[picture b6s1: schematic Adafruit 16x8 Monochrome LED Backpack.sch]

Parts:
A0, A1, A2: SOLDERJUMPERREFLOW_NOPASTE; SOLDERJUMPER_REFLOW_NOPASTE
C1, C2, C3: 10uF; 0805-NO
CN1: 1X4-CLEANBIG; 1X04-CLEANBIG
D1: 1N4148; SOD-323F
LED1, LED2: DISP_SEGMENT_8X8_ROWCATHODEM12A881UR; SEGMENT_BL-M12A881UR
R1: 10K; R0805
R2, R3, R4, R5: 10K; 0805-NO
U2: 28-SOIC; SOP28_300MIL
U$1, U$2: FIDUCIAL; FIDUCIAL_1MM

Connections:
A0: A0.2, LED1.4 (A3), U2.P$23 (ROW2/A0)
A1: A1.2, LED1.3 (A2), U2.P$24 (ROW1/A1)
A2: A2.2, LED1.13 (A1), U2.P$25 (ROW0/A2)
GND: C1.2, C2.2, C3.2, CN1.3, U2.P$1 (VSS)
unnamed: LED1.5 (K8), LED2.5 (K8), U2.P$9 (COM7)
unnamed: LED1.2 (K7), LED2.2 (K7), U2.P$8 (COM6)
unnamed: LED1.7 (K6), LED2.7 (K6), U2.P$7 (COM5)
unnamed: LED1.1 (K5), LED2.1 (K5), U2.P$6 (COM4)
unnamed: LED1.12 (K4), LED2.12 (K4), U2.P$5 (COM3/KS2)
unnamed: LED1.8 (K3), LED2.8 (K3), U2.P$4 (COM2/KS1)
unnamed: LED1.14 (K2), LED2.14 (K2), U2.P$3 (COM1/KS0)
unnamed: D1.A, LED1.9 (K1), LED2.9 (K1), U2.P$2 (COM0/AD)
unnamed: A2.1, R5.2
unnamed: LED2.15 (A7), U2.P$11 (ROW14/K12)
unnamed: LED2.11 (A6), U2.P$12 (ROW13/K11)
unnamed: LED2.16 (A8), U2.P$10 (ROW15/K13/INT)
unnamed: D1.C, R3.1, R4.1, R5.1
unnamed: A1.1, R3.2
unnamed: A0.1, R4.2
unnamed: LED1.16 (A8), U2.P$18 (ROW7/K5)
unnamed: LED1.15 (A7), U2.P$19 (ROW6/K4)
unnamed: LED1.6 (A5), U2.P$21 (ROW4/K2)
unnamed: LED1.10 (A4), U2.P$22 (ROW3/K1)
unnamed: LED1.11 (A6), U2.P$20 (ROW5/K3)
unnamed: LED2.13 (A1), U2.P$17 (ROW8/K6)
unnamed: LED2.3 (A2), U2.P$16 (ROW9/K7)
unnamed: LED2.10 (A4), U2.P$14 (ROW11/K9)
unnamed: LED2.4 (A3), U2.P$15 (ROW10/K8)
unnamed: LED2.6 (A5), U2.P$13 (ROW12/K10)
SCL: CN1.1, R1.2, U2.P$26 (SCL)
SDA: CN1.2, R2.2, U2.P$27 (SDA)
VDD: C1.1, C2.1, C3.1, CN1.4, R1.1, R2.1, U2.P$28 (VDD)

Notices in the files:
parts and their libraries:
microbuilder-pi: This work is placed in the public domain, and may be freely used for commercial and non-commercial work with the following conditions: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
